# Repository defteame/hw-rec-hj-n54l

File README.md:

# nrf54l15_hj_sip_recorder

A brand new atopile project!

Created by Pepper Powderly <pepper@atopile.io>

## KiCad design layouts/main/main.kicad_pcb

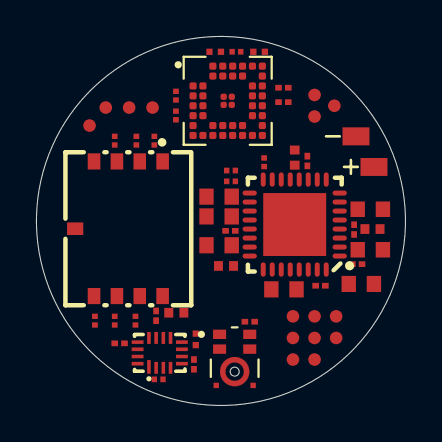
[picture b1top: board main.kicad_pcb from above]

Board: 4 copper layers, 20.5 x 20.5 mm, 60 parts (0 on the bottom side), 38 nets, no tracks yet.

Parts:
C1, C2, C18, C19, C22: 10µF ±10% 10V X5R; C0603
C5, C6, C7, C8, C9, C10, C12, C13, C14, C15, C17: 100nF ±10% X5R; C0201
C11: 2.2µF ±20% 6.3V X5R; C0402
C16, C20, C21: 1µF ±10% 25V X5R; C0402
C23, C24: DNP_CAP_0201
J_GND: BATTERY_PAD
J_VBAT: BATTERY_PAD
L1, L2: 2.2µH ±20% 750mA 240mΩ; L0603
M1: MIC_T5838
R1, R10: 0Ω 50mW; R0201
R2, R3: 4.7kΩ ±1% 50mW; R0201
R4, R11: 33Ω ±5% 50mW; R0201
R5, R6, R7, R8, R9: 10kΩ ±1% 50mW; R0201
R13: 47kΩ ±1% 50mW; R0201
R14: 150kΩ ±1% 50mW; R0201
R15: DNP_RES_0201
TP1, TP2, TP3, TP4, TP5, TP6, TP7, TP8, TP9, TP10, TP11, TP12, TP13, TP14, TP15: POGO_PAD
U1: XCVR_HJ-N54L_SIP
U2: LGA-8_L8.5-W7.0-P1.27-TL
U3: QFN-32_L5.0-W5.0-P0.50-TL-EP3.5
U4: UQFN-16_L2.6-W1.8-P0.40-BL

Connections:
A1: R11.1, U4.1
B1: U1.9, U4.12
B2: U1.11, U4.11
B3: U1.5, U4.10
B4: U1.6, U4.9
BOARD_ANT: C24.1, R1.2, U1.24
CD_SDD32: R9.1, TP9.1, U1.7, U2.2
CLK: M1.6, R11.2
CMD: R5.1, TP10.1, U1.30, U2.5
DATA: M1.1, R15.1, U4.2
GND: C1.2, C2.2, C5.2, C6.2, C7.2, C8.2, C9.2, C10.2, C11.2, C12.2, C13.2, C14.2, C15.2, C16.2, C17.2, C18.2, C19.2, C20.2, C21.2, C22.2, C23.2, C24.2, J_GND.1, M1.2, M1.31, M1.32, R10.2, R13.2, R14.2, R15.2, TP7.1, U1.19, U1.22, U1.25, U1.39, U2.4, U3.2, U3.6, U3.33, U4.5, U4.7, U4.8, U4.15
NRESET: TP14.1, U1.37
NTC: R10.1, U3.18
P1_02: R4.2, U1.8
P1_08: TP2.1, U1.10
P1_10: TP3.1, U1.18
RF: C23.1, R1.1, U1.23
SCL: R2.1, TP15.1, U1.27, U3.14
SCLK: R4.1, TP11.1, U2.3
SDA: R3.1, TP13.1, U1.26, U3.13
SDD1: R7.1, U2.7
SDD2: R8.1, U2.1
SDDO: R6.1, TP12.1, U1.33, U2.6
SHPHLD: TP5.1, U3.15
SW1: L1.1, U3.3
SW2: L2.1, U3.5
SWDCLK: TP1.1, U1.28
SWDIO: TP4.1, U1.2
THSEL: M1.5, U4.3
VBAT: C18.1, J_VBAT.1, U3.19
VBUS: C12.1, C19.1, TP8.1, U3.21
VBUSOUT: C20.1, U3.22
VCC: C2.1, C6.1, C7.1, C8.1, C10.1, C11.1, C13.1, C15.1, C21.1, L2.2, R2.2, R3.2, R5.2, R6.2, R7.2, R8.2, R9.2, TP6.1, U1.42, U1.43, U1.44, U1.45, U2.8, U3.12, U3.32, U4.13
VCCA: C1.1, C5.1, C9.1, C14.1, L1.2, M1.7, U3.1, U4.6, U4.14, U4.16
VSET1: R13.1, U3.17
VSET2: R14.1, U3.16
VSYS: C16.1, C17.1, C22.1, U3.4, U3.20
WAKE: M1.4, U4.4

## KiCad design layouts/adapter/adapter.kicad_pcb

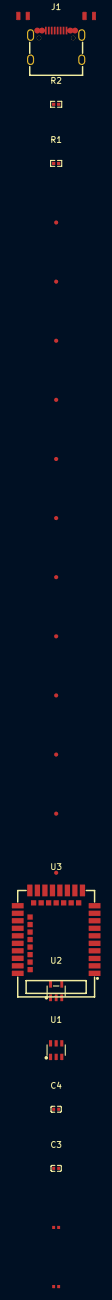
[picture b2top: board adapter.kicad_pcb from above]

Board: 2 copper layers, 22 parts (0 on the bottom side), 15 nets, no tracks yet.

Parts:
C1, C2: 1µF ±10% 25V X5R; C0402
C3, C4: 100nF ±10% 16V X7R; C0402
J1: USB-C_SMD-TYPE-C-31-M-12_1
R1, R2: 5.1kΩ ±1% 62.5mW; R0402
TP1, TP2, TP3, TP4, TP5, TP6, TP7, TP8, TP9, TP10, TP11, TP12: POGO_PAD
U1: SOT-23-6_L2.9-W1.6-P0.95-LS2.8-BL
U2: SOT-23-5_L3.0-W1.7-P0.95-LS2.8-BL
U3: WIRELM-SMD_E73-2G4M08S1C

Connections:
A5: J1.A5, R1.1
B5: J1.B5, R2.1
D_minus: J1.A7, J1.B7, U3.29
D_plus: J1.A6, J1.B6, U3.31
GND: C1.2, C2.2, C3.2, C4.2, J1.1, J1.2, J1.3, J1.4, J1.A1B12, R1.2, R2.2, TP2.1, TP3.1, TP4.1, U2.2, U3.5, U3.21, U3.24
POGO_3V3_SENSE: TP1.1, U3.7
POGO_I2C_SCL: TP5.1, U3.35
POGO_I2C_SDA: TP6.1, U3.12
POGO_RESET: TP7.1, U3.34
POGO_SWDCLK: TP8.1, U3.32
POGO_SWDIO: TP9.1, U3.33
POGO_UART_RX: TP10.1, U3.16
POGO_UART_TX: TP11.1, U3.14
VBUS: C1.1, J1.A4B9, TP12.1, U2.1, U2.3, U3.27
VCC: C2.1, C3.1, C4.1, U2.5, U3.19, U3.23

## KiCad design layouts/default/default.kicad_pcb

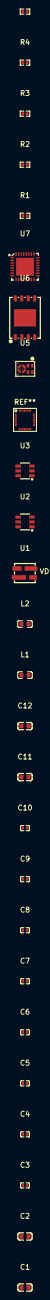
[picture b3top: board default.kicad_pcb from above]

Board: 2 copper layers, 26 parts (0 on the bottom side), 22 nets, no tracks yet.

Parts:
C1, C2, C11, C12: 10µF ±10% 10V X5R; C0603
C3, C4, C5, C6, C7, C8, C9, C10: 100nF ±10% 16V X7R; C0402
L1, L2: 2.2µH ±20% 750mA 240mΩ; L0603
R1, R2: 33Ω ±1% 62.5mW; R0402
R3, R4, R5: 47kΩ ±1% 62.5mW; R0402
U1: LED-SMD_4P-L3.7-W3.5-P1.75-BR-SK6812MINI
U2, U3: SOT-23-6_L2.9-W1.6-P0.95-LS2.8-BR
U4: HJ_N54L_SIP
U5: MIC-SMD_7P-L3.5-W2.7_MMICT5837-00-012
U6: WSON-8_L8.0-W6.0-P1.27-BL-EP-1
U7: QFN-32_L5.0-W5.0-P0.50-TL-EP3.5

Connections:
CLK: R2.1, U6.3
CMD: U4.13, U6.5
DAT0: U4.14, U6.6
DAT1: R3.1, U6.7
DAT2: R4.1, U6.1
DAT3: R5.1, U6.2
DIN: R1.2, U1.1
GND: C1.2, C2.2, C3.2, C4.2, C5.2, C6.2, C7.2, C8.2, C9.2, C10.2, C11.2, C12.2, U1.4, U2.2, U2.5, U3.2, U4.2, U4.19, U4.20, U5.2, U5.3, U5.5, U6.4, U6.9, U7.2, U7.6, U7.33
LED_DATA: R1.1, U4.18
NAND_CLK: R2.2, U4.12
PAD_I2C_SCL: U4.9, U7.14
PAD_I2C_SDA: U4.8, U7.13
SW1: L1.1, U7.3
SW2: L2.1, U7.5
VBAT: C11.1, U7.4, U7.19, U7.20
VBUS: C12.1, U7.21
VCCA: C1.1, C3.1, C5.1, C9.1, L2.2, U2.1, U3.1, U5.4, U5.7, U7.32
VDD: C2.1, C4.1, C6.1, C7.1, C8.1, C10.1, L1.2, R3.2, R4.2, R5.2, U1.2, U2.6, U3.5, U3.6, U4.1, U6.8, U7.1, U7.12, U7.15
footprint-A-0: U2.3, U5.6
footprint-A-1: U3.3, U5.1
footprint-B-0: U2.4, U4.10
footprint-B-1: U3.4, U4.11

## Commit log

2026-01-23 add circle outline
2026-01-24 change board stackup to 4 layers and set thickness to 0,4mm
2026-01-24 add min constraints
2026-01-24 wip text sizesmfix
2026-01-24 r1 placed
2026-01-24 wip rough placement
2026-01-24 change silkscreen text size
2026-01-24 smaller pogo footprints
2026-01-25 drc rules
2026-01-25 wpip
2026-01-25 assign reference designators to mcu and mic
2026-01-25 wip - footprint
2026-01-25 wip footprint
2026-01-25 wip ato build
2026-01-25 footprints edit
2026-01-25 fp edit
2026-01-25 wip silk
2026-01-25 Main designators
